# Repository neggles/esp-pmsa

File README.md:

# esp-pmsa

## Repository Structure
- `esp-pmsa` contains the main schematics and board drawing
- `esp-pmsa/esp-pmsa.pretty` contains the board-specific footprints
- `esp-pmsa/shapes3D` contains the 3D models for parts on the board (and a bunch of extras from my various experiments)

## Building
Simply call `make` in the top-top level directory. The `build` directory will then contain:

- the main board
- A panelized version of said board
- zipped gerbers for the boards you can directly use for manufacturing
- zipped gerbers and SMT assembly BOM/position files for JLCPCB's SMT assembly service for the single-board version.

Makefile uses [Jan Mrázek](https://github.com/yaqwsx)'s [KiKit](https://github.com/yaqwsx/KiKit), which I cannot recommend enough, and therefore has to be available on your system.

Jan's [jlcparts](https://yaqwsx.github.io/jlcparts/) app was also extremely useful in narrowing down part choices based on what JLCPCB have available.

-----
### **IMPORTANT NOTE:** If you give JLCPCB these files as-is, *please* verify the orientation of every part before submitting.

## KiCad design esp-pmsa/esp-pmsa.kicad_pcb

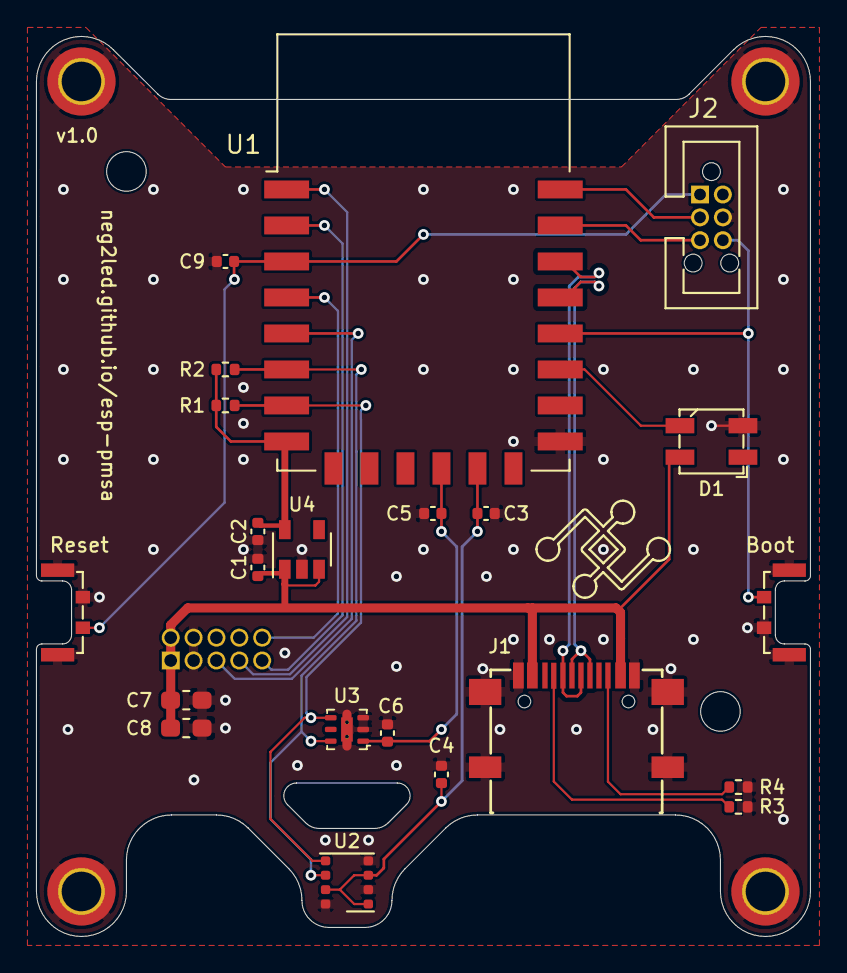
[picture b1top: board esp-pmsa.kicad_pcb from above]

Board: 2 copper layers, 43.0 x 50.0 mm, 28 parts (1 on the bottom side), 20 nets.

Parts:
C1, C2: 10u; C_0402_1005Metric
C3, C5: 1u; C_0402_1005Metric
C4, C6, C9: 0.1u; C_0402_1005Metric
C7, C8: 10u; C_0603_1608Metric_Pad1.05x0.95mm_HandSolder
D1: APA104-12-3535; LED_APA104-12-3535
H1, H2, H3, H4: MP; MountingHole_2.2mm_M2_DIN965_Pad_TopBottom
J1: USB-C; USB-C-SMD_TYPEC-304S-ACP16
J2: ESP-PROG; TC2030_IDCBox_2x03_P1.25mm_Vertical_3D
LOGO1: neggles logo; neggle-logo-0.12
M1: PMSA003
R1, R2: 4k7; R_0402_1005Metric
R3, R4: 5k1; R_0402_1005Metric
SW1: Reset; SW-SMD_SKSLLAE010-3D
SW2: Boot; SW-SMD_SKSLLAE010-3D
U1: ESP32-C3F; ESP-12H
U2: BME68x; Bosch_LGA-8_3x3mm_P0.8mm_ClockwisePinNumbering
U3: OPT3001DNPT; MultiALS-LTR303-TIOPT3K
U4: XC6210B332MR; SOT-23-5

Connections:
+3V3: C2.1, R1.1, R2.1, U1.8 (VCC), U4.5 (VOUT)
+5V: C1.2, C7.1, C8.1, D1.4 (VDD), J1.A4B9 (VBUS), J1.B4A9 (VBUS), M1.1 (VCC), M1.2 (VCC), U4.1 (VIN), U4.3 (CE)
/PMS_RX: M1.7 (RXD), U1.1 (IO0)
/PMS_TX: M1.9 (TXD), U1.2 (IO1)
/RGB: D1.3 (DIN), U1.17 (IO10)
/SCL: R1.2, U1.7 (MTDI/IO5), U2.4 (SCK), U3.4 (SCL)
/SDA: R2.2, U1.6 (MTMS/IO4), U2.3 (SDI), U3.6 (SDA)
/U0RXD: J2.5, U1.21 (IO20/U0RX)
/U0TXD: J2.3, U1.22 (IO21/U0TX)
/USB_D+: J1.A6 (D+), J1.B6 (D+), U1.19 (IO19/D+)
/USB_D-: J1.A7 (D-), J1.B7 (D-), U1.20 (IO18/D-)
/VCC_ALS: C5.1, C6.1, U1.12 (MTCK/IO6), U3.1 (VDD)
/VCC_BME: C3.1, C4.1, U1.13 (MTDO/IO7), U2.2 (CSB), U2.6 (VDDIO), U2.8 (VDD)
/~BOOT: J2.6, SW2.2, U1.18 (IO9/~BOOT)
/~PMS_RST: M1.5 (~RST), U1.5 (IO3)
/~PMS_SET: M1.10 (~SET), U1.4 (IO2)
/~RST: C9.2, J2.1, SW1.2, U1.3 (EN)
GND: C1.1, C2.2, C3.2, C4.2, C5.2, C6.2, C7.2, C8.2, C9.1, D1.2 (VSS), H1.1, H2.1, H3.1, H4.1, J1.A1B12 (GND), J1.B1A12 (GND), J1.S1 (SHIELD), J2.4, M1.3 (GND), M1.4 (GND), R3.1, R4.1, SW1.1, SW1.MP, SW2.1, SW2.MP, U1.15 (GND), U2.1 (GND), U2.5 (SDO), U2.7 (GND), U3.2 (ADR), U3.3 (GND), U3.7 (GND), U4.2 (GND)
unnamed: J1.A5 (CC1), R3.2
unnamed: J1.B5 (CC2), R4.2

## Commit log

2021-04-13 still needs routing
2021-04-13 add gnd zones
2021-04-14 ok this is silly
2021-04-14 KISS
2021-04-15 still don't like
2021-04-15 v0.1
2021-04-15 add png
2021-04-15 fix action
2021-04-15 Initial gh-pages commit
2021-04-15 Deploying to gh-pages from @ neg2led/esp-pmsa@a730e507301c682fc7d8a88894b304163d40722a 🚀
2021-04-15 update badge to not be travis
2021-04-15 Deploying to gh-pages from @ neg2led/esp-pmsa@060c7214fca1917f5e98065bfc5be80db49c411f 🚀
2021-04-15 fix pour
2021-04-15 Deploying to gh-pages from @ neg2led/esp-pmsa@5249862c854155dbbe1c443dd720162530209050 🚀
2021-04-16 minor project file bump
2021-04-16 Deploying to gh-pages from @ neg2led/esp-pmsa@9632b926f083bace6a9f50f507fc2e692adbb89b 🚀
2021-04-18 license update
2021-04-18 Deploying to gh-pages from @ neg2led/esp-pmsa@8cfb15ab658ebe3677a417a23ec310706aeae942 🚀
2021-04-26 add build i guess
2021-04-26 tweak
2021-04-26 add pdf
2021-04-26 Deploying to gh-pages from @ neg2led/esp-pmsa@d9161fd97d49d904e7352142a6cfa9bb73c8df2b 🚀
2021-08-11 switch to ESP-C3-F
2021-08-11 Deploying to gh-pages from @ neg2led/esp-pmsa@e03a36f01e21f29b520752c6169685313d9a0f2f 🚀
2021-08-21 okeydokey!
2021-08-21 Deploying to gh-pages from @ neg2led/esp-pmsa@1a288ce33808fbc405a6c24b3a385c7c225d67b1 🚀
2021-08-21 Deploying to gh-pages from @ neg2led/esp-pmsa@f8f0e89e197d9d7cec6abac82e6cbc78cb6912ec 🚀
2021-08-21 layout tweaks
2021-08-21 Deploying to gh-pages from @ neg2led/esp-pmsa@53209a84ec166707ba2d67fc5a12d877258f9ac0 🚀
2021-08-21 okay that's better
2021-08-21 Deploying to gh-pages from @ neg2led/esp-pmsa@5792303937cde9c3b92ca60e7ea9c0f6023d491c 🚀
2021-09-23 update for kicad 6
2021-10-14 clean up old v5 files a bit, theres more i can delete
2021-10-23 actually built ver
2022-11-22 add .gitattributes
